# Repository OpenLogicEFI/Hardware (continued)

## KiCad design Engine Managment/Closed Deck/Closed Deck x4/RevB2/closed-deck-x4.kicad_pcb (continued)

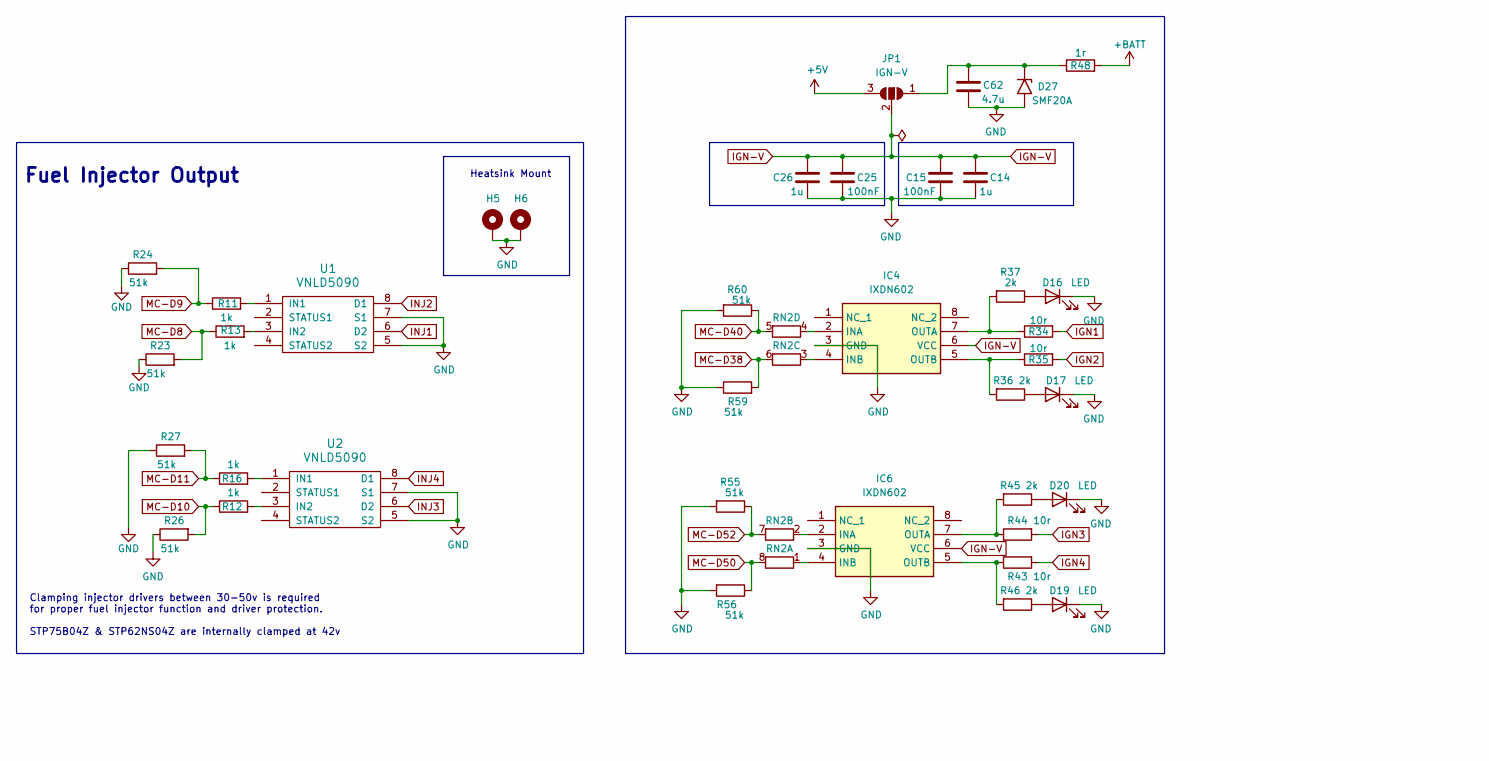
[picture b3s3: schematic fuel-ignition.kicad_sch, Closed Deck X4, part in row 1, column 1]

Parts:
C14, C26: 1u; C_0402_1005Metric; LCSC C52923
C15, C25: 100nF; C_0402_1005Metric; LCSC C307331
C62: 4.7u; C_1206_3216Metric; Manufacture Part Number 1206B475K500NT; LCSC C29823
D16, D17, D19, D20: LED; LED_0603_1608Metric; Manufacture Part Number KT-0603R; LCSC C2286
D27: SMF20A; D_SMF; LCSC C41411782
H5, H6: MountingHole_Pad; MountingHole_CD_Heatsink
IC4, IC6: IXDN602; SOIC-8_3.9x4.9mm_P1.27mm; Manufacture Part Number IXDN602; LCSC C431679
JP1: IGN-V; 1x03-Proto
R11, R12, R13, R16: 1k; R_0402_1005Metric; Manufacture Part Number 0402WGF1001TCE; LCSC C11702
R23, R24, R26, R27, R55, R56, R59, R60: 51k; R_0402_1005Metric; Manufacture Part Number 0402WGF5102TCE; LCSC C25794
R34, R35, R43, R44: 10r; R_0805_2012Metric; Manufacture Part Number 0805W8F100JT5E; LCSC C17415
R36, R37, R45, R46: 2k; R_0402_1005Metric; Manufacture Part Number 0402WGF2001TCE; LCSC C4109
R48: 1r; R_1206_3216Metric; Manufacture Part Number 1206W4F100KT5E; LCSC C17928
RN2: 1k; R_Array_Concave_4x0603; Manufacture Part Number 4D03WGJ0102T5E; LCSC C20197
U1, U2: VNLD5090; SO-8_3.9x4.9mm_P1.27mm_HandSoldering; LCSC C222209

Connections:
+5V: JP1.3 (B); also elsewhere on the board
+BATT: R48.2; also elsewhere on the board
GND: C14.2, C15.2, C25.2, C26.2, C62.2, D16.1 (K), D17.1 (K), D19.1 (K), D20.1 (K), D27.2 (A2), H5.1 (1_1), H6.1 (1_1), IC4.3 (GND), IC6.3 (GND), R23.1, R24.1, R26.1, R27.1, R55.2, R56.2, R59.1, R60.2, U1.5 (S2), U1.7 (S1), U2.5 (S2), U2.7 (S1); also elsewhere on the board
IGN1: R34.2; also elsewhere on the board
IGN2: R35.2; also elsewhere on the board
IGN3: R44.2; also elsewhere on the board
IGN4: R43.2; also elsewhere on the board
IGN-V: C14.1, C15.1, C25.1, C26.1, IC4.6 (VCC), IC6.6 (VCC), JP1.2 (C)
INJ1: U1.6 (D2); also elsewhere on the board
INJ2: U1.8 (D1); also elsewhere on the board
INJ3: U2.6 (D2); also elsewhere on the board
INJ4: U2.8 (D1); also elsewhere on the board
MC-D8: R13.1, R23.2; also elsewhere on the board
MC-D9: R11.1, R24.2; also elsewhere on the board
MC-D10: R12.1, R26.2; also elsewhere on the board
MC-D11: R16.1, R27.2; also elsewhere on the board
MC-D38: R59.2, RN2.6 (R3.2); also elsewhere on the board
MC-D40: R60.1, RN2.5 (R4.2); also elsewhere on the board
MC-D50: R56.1, RN2.8 (R1.2); also elsewhere on the board
MC-D52: R55.1, RN2.7 (R2.2); also elsewhere on the board
unnamed: D16.2 (A), R37.1
unnamed: D17.2 (A), R36.1
unnamed: D19.2 (A), R46.1
unnamed: D20.2 (A), R45.1
unnamed: C62.1, D27.1 (A1), JP1.1 (A), R48.1
unnamed: IC4.2 (INA), RN2.4 (R4.1)
unnamed: IC4.4 (INB), RN2.3 (R3.1)
unnamed: IC4.7 (OUTA), R34.1, R37.2
unnamed: IC4.5 (OUTB), R35.1, R36.2
unnamed: IC6.2 (INA), RN2.2 (R2.1)
unnamed: IC6.4 (INB), RN2.1 (R1.1)
unnamed: IC6.7 (OUTA), R44.1, R45.2
unnamed: IC6.5 (OUTB), R43.1, R46.2
unnamed: R11.2, U1.1 (IN1)
unnamed: R13.2, U1.3 (IN2)
unnamed: R16.2, U2.1 (IN1)
unnamed: R12.2, U2.3 (IN2)

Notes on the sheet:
Heatsink Mount
Clamping injector drivers between 30-50v is required for proper fuel injector function and driver protection. STP75B04Z & STP62NS04Z are internally clamped at 42v
Fuel Injector Output
Logic Level Ignition Output

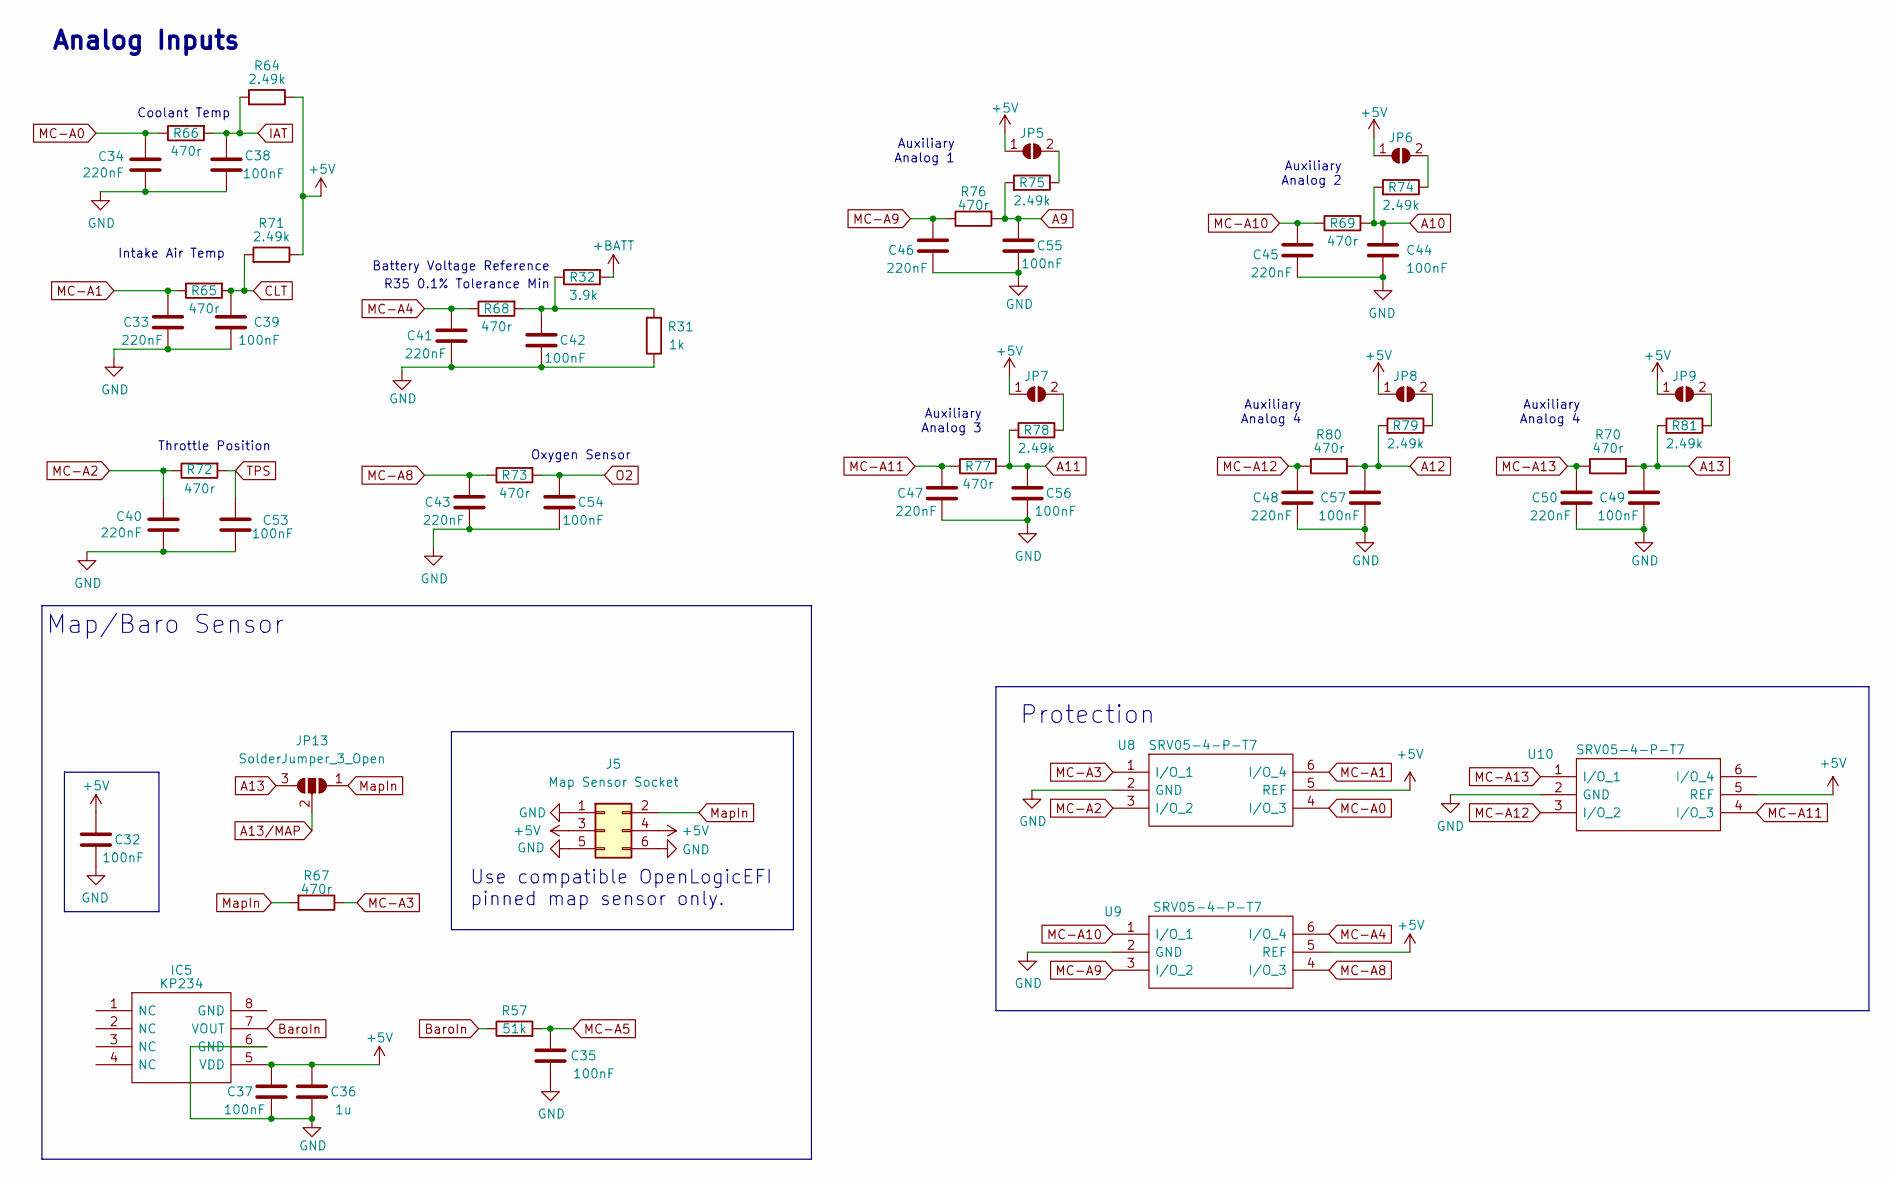
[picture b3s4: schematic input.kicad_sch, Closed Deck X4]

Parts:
C32, C37, C38, C39, C42, C44, C49, C53, C54, C55, C56, C57: 100nF; C_0402_1005Metric; LCSC C307331
C33, C34, C40, C41, C43, C45, C46, C47, C48, C50: 220nF; C_0402_1005Metric; LCSC C16772
C35: 100nF; C_0402_1005Metric; Manufacture Part Number CL05B104KB54PNC; LCSC C307331
C36: 1u; C_0402_1005Metric; LCSC C52923
IC5: KP234; KP234-Handsoldering; Manufacture Part Number KP234XTMA1
J5: Map Sensor Socket; PinSocket 2x03
JP5, JP6, JP7, JP8, JP9: SolderJumper_2_Open; SolderJumper-2_P1.3mm_Open_RoundedPad1.0x1.5mm
JP13: SolderJumper_3_Open; SolderJumper-3-OPEN
R31: 1k; R_0402_1005Metric; Manufacture Part Number 0402WGF1001TCE; LCSC C11702
R32: 3.9k; R_0603_1608Metric; Manufacture Part Number 0603WAF3901T5E; LCSC C23018
R57: 51k; R_0402_1005Metric; Manufacture Part Number 0402WGF5102TCE; LCSC C25794
R64, R71: 2.49k; R_Axial_DIN0207_L6.3mm_D2.5mm_P7.62mm_Horizontal
R65, R66, R67, R68, R69, R70, R72, R73, R76, R77, R80: 470r; R_0402_1005Metric; Manufacture Part Number 0402WGF4700TCE; LCSC C25117
R74, R75, R78, R79, R81: 2.49k; R_0402_1005Metric; Manufacture Part Number RC0402FR-072K49L; LCSC C145071
U8, U9, U10: SRV05-4-P-T7; SOT-23-6; LCSC C85364

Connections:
+5V: C32.2, C36.1, C37.1, IC5.5 (VDD), J5.3, J5.4, JP5.1 (A), JP6.1 (A), JP7.1 (A), JP8.1 (A), JP9.1 (A), R64.1, R71.1, U8.5 (REF), U9.5 (REF), U10.5 (REF); also elsewhere on the board
+BATT: R32.2; also elsewhere on the board
A9: C55.1, R75.2, R76.2; also elsewhere on the board
A10: C44.1, R69.2, R74.2; also elsewhere on the board
A11: C56.1, R77.2, R78.2; also elsewhere on the board
A12: C57.1, R79.2, R80.2; also elsewhere on the board
A13: C49.1, JP13.3 (B), R70.2, R81.2
A13/MAP: JP13.2 (C); also elsewhere on the board
BaroIn: IC5.7 (VOUT), R57.1
CLT: C39.1, R65.2, R71.2; also elsewhere on the board
GND: C32.1, C33.2, C34.2, C35.2, C36.2, C37.2, C38.2, C39.2, C40.2, C41.2, C42.2, C43.2, C44.2, C45.2, C46.2, C47.2, C48.2, C49.2, C50.2, C53.2, C54.2, C55.2, C56.2, C57.2, IC5.6 (GND), J5.1, J5.5, J5.6, R31.1, U8.2 (GND), U9.2 (GND), U10.2 (GND); also elsewhere on the board
IAT: C38.1, R64.2, R66.2; also elsewhere on the board
MC-A0: C34.1, R66.1, U8.4 (I/O_3); also elsewhere on the board
MC-A1: C33.1, R65.1, U8.6 (I/O_4); also elsewhere on the board
MC-A2: C40.1, R72.1, U8.3 (I/O_2); also elsewhere on the board
MC-A3: R67.1, U8.1 (I/O_1); also elsewhere on the board
MC-A4: C41.1, R68.1, U9.6 (I/O_4); also elsewhere on the board
MC-A5: C35.1, R57.2; also elsewhere on the board
MC-A8: C43.1, R73.1, U9.4 (I/O_3); also elsewhere on the board
MC-A9: C46.1, R76.1, U9.3 (I/O_2); also elsewhere on the board
MC-A10: C45.1, R69.1, U9.1 (I/O_1); also elsewhere on the board
MC-A11: C47.1, R77.1, U10.4 (I/O_3); also elsewhere on the board
MC-A12: C48.1, R80.1, U10.3 (I/O_2); also elsewhere on the board
MC-A13: C50.1, R70.1, U10.1 (I/O_1); also elsewhere on the board
MapIn: J5.2, JP13.1 (A), R67.2
unnamed: C42.1, R31.2, R32.1, R68.2
unnamed: JP5.2 (B), R75.1
unnamed: JP6.2 (B), R74.1
unnamed: JP7.2 (B), R78.1
unnamed: JP8.2 (B), R79.1
unnamed: JP9.2 (B), R81.1
O2: C54.1, R73.2; also elsewhere on the board
TPS: C53.1, R72.2; also elsewhere on the board

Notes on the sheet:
Analog Inputs
Throttle Position
Auxiliary Analog 2
Auxiliary Analog 4
Auxiliary Analog 1
R35 0.1% Tolerance Min
Oxygen Sensor
Map/Baro Sensor
Use compatible OpenLogicEFI pinned map sensor only.
Coolant Temp
Intake Air Temp
Battery Voltage Reference
Protection
Auxiliary Analog 3

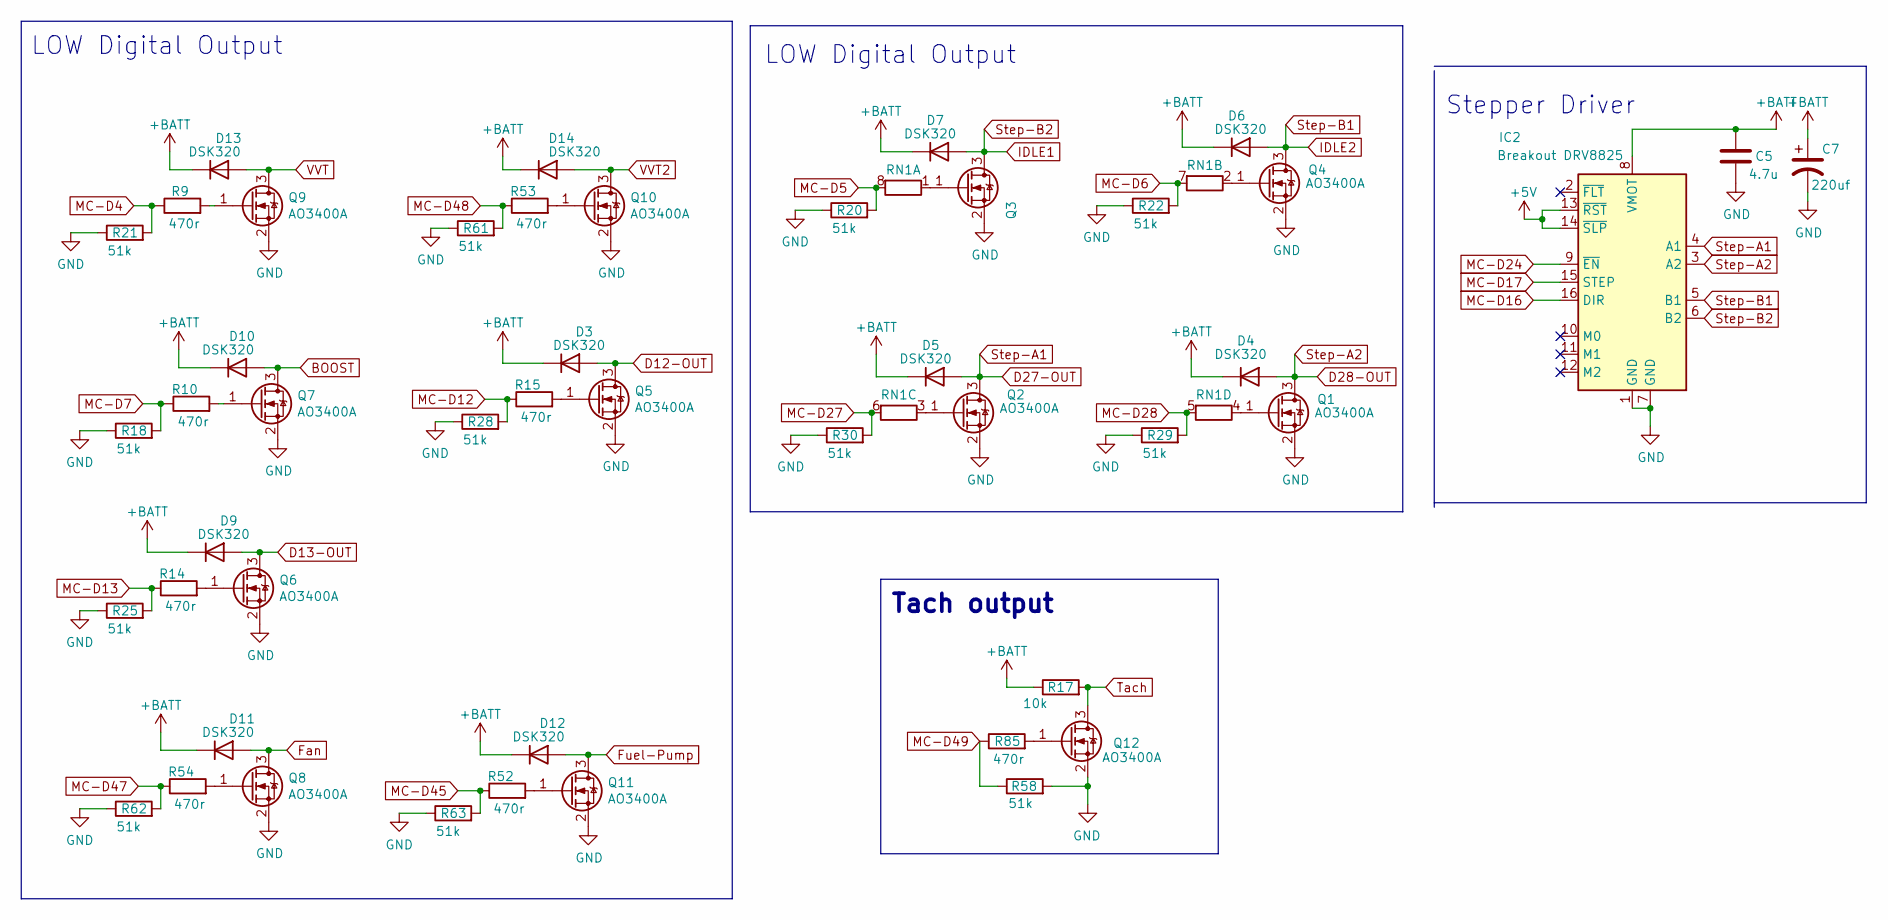
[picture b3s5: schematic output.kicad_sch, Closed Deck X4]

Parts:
C5: 4.7u; C_1206_3216Metric; Manufacture Part Number 1206B475K500NT; LCSC C29823
C7: 220uf; CP_Radial_D6.3mm_P2.50mm
D3, D4, D5, D6, D7, D9, D10, D11, D12, D13, D14: DSK320; D_SOD-123F; JLC C2128
IC2: Breakout DRV8825; DVR8825-Labeled-Front
Q1, Q2, Q3, Q4, Q5, Q6, Q12: AO3400A; SOT-23; Manufacture Part Number AO3400A; LCSC C20917
Q7, Q8, Q9, Q10, Q11: AO3400A; SOT-23; Manufacture Part Number AO3400A; JLC C20917
R9, R10, R14, R15, R52, R53, R54, R85: 470r; R_0402_1005Metric; Manufacture Part Number 0402WGF4700TCE; LCSC C25117
R17: 10k; R_0402_1005Metric; Manufacture Part Number 0402WGF1002TCE; LCSC C25744
R18, R20, R21, R22, R25, R28, R29, R30, R58, R61, R62, R63: 51k; R_0402_1005Metric; Manufacture Part Number 0402WGF5102TCE; LCSC C25794
RN1: 1k; R_Array_Concave_4x0603; Manufacture Part Number 4D03WGJ0102T5E; LCSC C20197

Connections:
+5V: IC2.13 (~RST), IC2.14 (~SLP); also elsewhere on the board
+BATT: C5.1, C7.1, D3.1 (K), D4.1 (K), D5.1 (K), D6.1 (K), D7.1 (K), D9.1 (K), D10.1 (K), D11.1 (K), D12.1 (K), D13.1 (K), D14.1 (K), IC2.8 (VMOT), R17.1; also elsewhere on the board
BOOST: D10.2 (A), Q7.3 (D); also elsewhere on the board
D12-OUT: D3.2 (A), Q5.3 (D); also elsewhere on the board
D13-OUT: D9.2 (A), Q6.3 (D); also elsewhere on the board
D27-OUT: D5.2 (A), IC2.4 (A1), Q2.3 (D); also elsewhere on the board
D28-OUT: D4.2 (A), IC2.3 (A2), Q1.3 (D); also elsewhere on the board
Fan: D11.2 (A), Q8.3 (D); also elsewhere on the board
Fuel-Pump: D12.2 (A), Q11.3 (D); also elsewhere on the board
GND: C5.2, C7.2, IC2.1 (GND), IC2.7 (GND), Q1.2 (S), Q2.2 (S), Q3.2 (S), Q4.2 (S), Q5.2 (S), Q6.2 (S), Q7.2 (S), Q8.2 (S), Q9.2 (S), Q10.2 (S), Q11.2 (S), Q12.2 (S), R18.1, R20.1, R21.1, R22.1, R25.1, R28.1, R29.1, R30.1, R58.2, R61.1, R62.1, R63.1; also elsewhere on the board
IDLE1: D7.2 (A), IC2.6 (B2), Q3.3 (D); also elsewhere on the board
IDLE2: D6.2 (A), IC2.5 (B1), Q4.3 (D); also elsewhere on the board
MC-D4: R9.1, R21.2; also elsewhere on the board
MC-D5: R20.2, RN1.8 (R1.2); also elsewhere on the board
MC-D6: R22.2, RN1.7 (R2.2); also elsewhere on the board
MC-D7: R10.1, R18.2; also elsewhere on the board
MC-D12: R15.1, R28.2; also elsewhere on the board
MC-D13: R14.1, R25.2; also elsewhere on the board
MC-D16: IC2.16 (DIR); also elsewhere on the board
MC-D17: IC2.15 (STEP); also elsewhere on the board
MC-D24: IC2.9 (~EN); also elsewhere on the board
MC-D27: R30.2, RN1.6 (R3.2); also elsewhere on the board
MC-D28: R29.2, RN1.5 (R4.2); also elsewhere on the board
MC-D45: R52.1, R63.2; also elsewhere on the board
MC-D47: R54.1, R62.2; also elsewhere on the board
MC-D48: R53.1, R61.2; also elsewhere on the board
MC-D49: R58.1, R85.1; also elsewhere on the board
unnamed: Q1.1 (G), RN1.4 (R4.1)
unnamed: Q2.1 (G), RN1.3 (R3.1)
unnamed: Q3.1 (G), RN1.1 (R1.1)
unnamed: Q4.1 (G), RN1.2 (R2.1)
unnamed: Q5.1 (G), R15.2
unnamed: Q6.1 (G), R14.2
unnamed: Q7.1 (G), R10.2
unnamed: Q8.1 (G), R54.2
unnamed: Q9.1 (G), R9.2
unnamed: Q10.1 (G), R53.2
unnamed: Q11.1 (G), R52.2
unnamed: Q12.1 (G), R85.2
Tach: Q12.3 (D), R17.2; also elsewhere on the board
VVT: D13.2 (A), Q9.3 (D); also elsewhere on the board
VVT2: D14.2 (A), Q10.3 (D); also elsewhere on the board

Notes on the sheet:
Tach output
LOW Digital Output
Stepper Driver

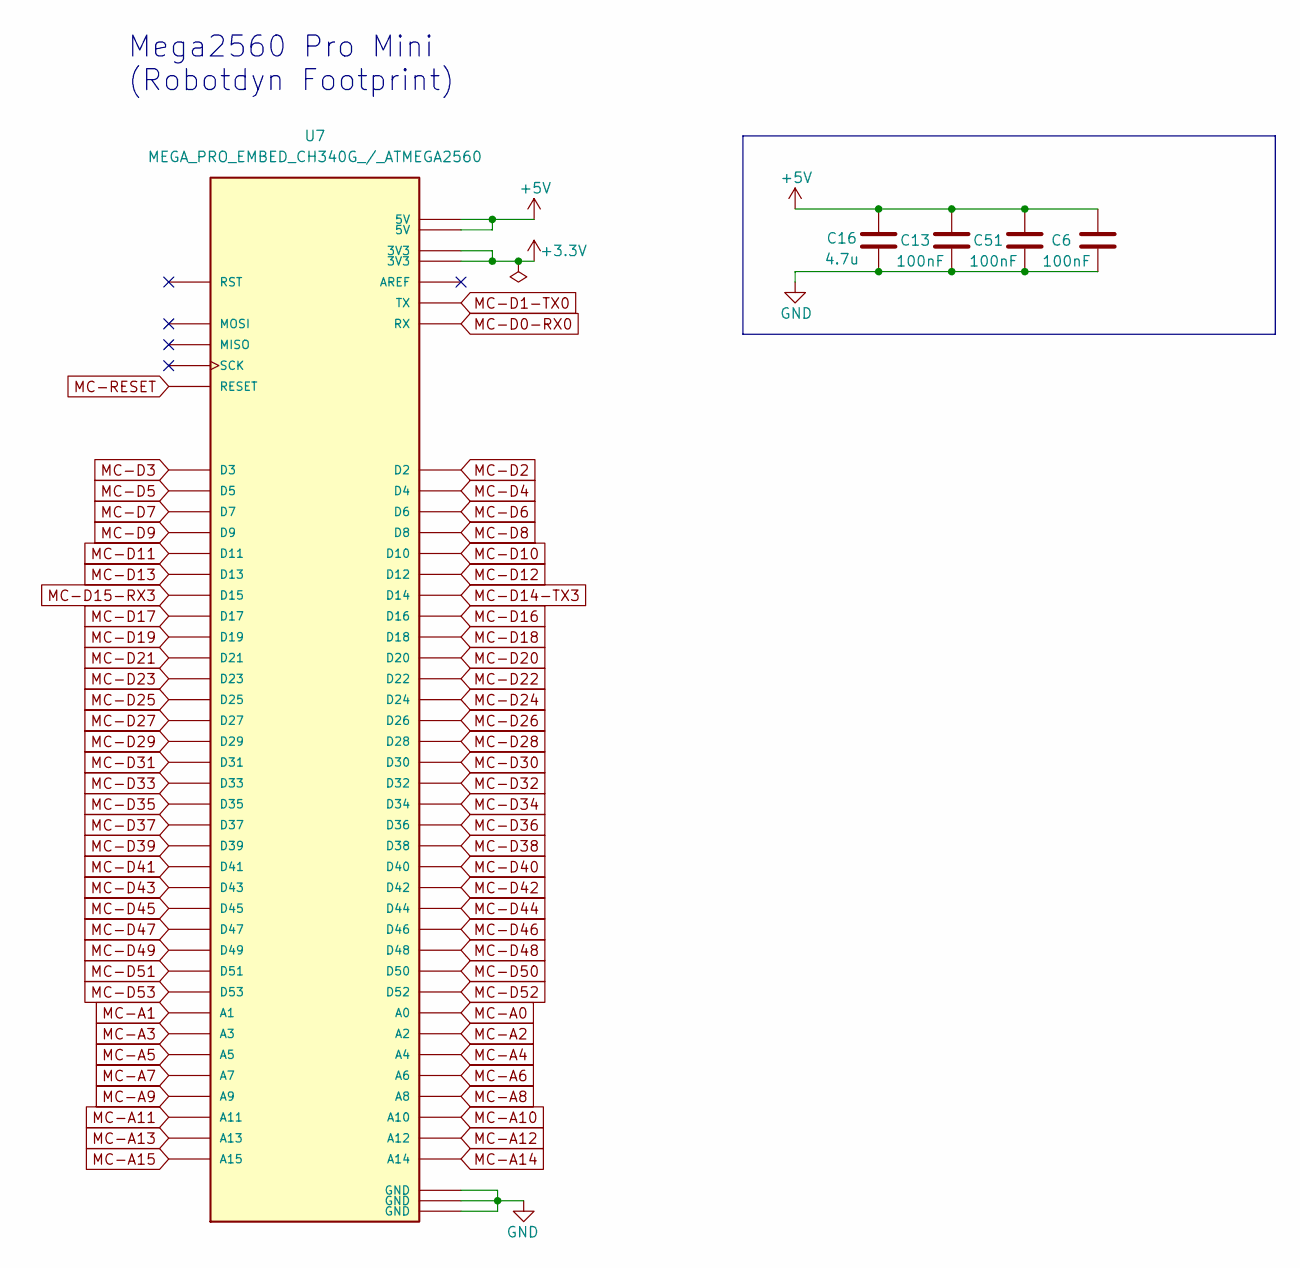
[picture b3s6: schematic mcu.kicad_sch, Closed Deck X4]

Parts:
C6, C13, C51: 100nF; C_0402_1005Metric; LCSC C307331
C16: 4.7u; C_1206_3216Metric; Manufacture Part Number 1206B475K500NT; LCSC C29823
U7: MEGA_PRO_EMBED_CH340G_/_ATMEGA2560; Arduino_Mega_Mini_2560_SmallCrtYd_NoVin

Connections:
+3.3V: U7.3V3_1 (3V3), U7.3V3_2 (3V3)
+5V: C6.2, C13.2, C16.1, C51.2, U7.5V_1 (5V), U7.5V_2 (5V), U7.5V_3 (5V); also elsewhere on the board
GND: C6.1, C13.1, C16.2, C51.1, U7.GND_1 (GND), U7.GND_2 (GND), U7.GND_3 (GND); also elsewhere on the board
MC-A0: U7.A0; also elsewhere on the board
MC-A1: U7.A1; also elsewhere on the board
MC-A2: U7.A2; also elsewhere on the board
MC-A3: U7.A3; also elsewhere on the board
MC-A4: U7.A4; also elsewhere on the board
MC-A5: U7.A5; also elsewhere on the board
MC-A6: U7.A6
MC-A7: U7.A7
MC-A8: U7.A8; also elsewhere on the board
MC-A9: U7.A9; also elsewhere on the board
MC-A10: U7.A10; also elsewhere on the board
MC-A11: U7.A11; also elsewhere on the board
MC-A12: U7.A12; also elsewhere on the board
MC-A13: U7.A13; also elsewhere on the board
MC-A14: U7.A14
MC-A15: U7.A15
MC-D0-RX0: U7.RX; also elsewhere on the board
MC-D1-TX0: U7.TX; also elsewhere on the board
MC-D2: U7.D2; also elsewhere on the board
MC-D3: U7.D3; also elsewhere on the board
MC-D4: U7.D4; also elsewhere on the board
MC-D5: U7.D5; also elsewhere on the board
MC-D6: U7.D6; also elsewhere on the board
MC-D7: U7.D7; also elsewhere on the board
MC-D8: U7.D8; also elsewhere on the board
MC-D9: U7.D9; also elsewhere on the board
MC-D10: U7.D10; also elsewhere on the board
MC-D11: U7.D11; also elsewhere on the board
MC-D12: U7.D12; also elsewhere on the board
MC-D13: U7.D13; also elsewhere on the board
MC-D14-TX3: U7.D14; also elsewhere on the board
MC-D15-RX3: U7.D15; also elsewhere on the board
MC-D16: U7.D16; also elsewhere on the board
MC-D17: U7.D17; also elsewhere on the board
MC-D18: U7.D18; also elsewhere on the board
MC-D19: U7.D19; also elsewhere on the board
MC-D20: U7.D20; also elsewhere on the board
MC-D21: U7.D21; also elsewhere on the board
MC-D22: U7.D22; also elsewhere on the board
MC-D23: U7.D23; also elsewhere on the board
MC-D24: U7.D24; also elsewhere on the board
MC-D25: U7.D25
MC-D26: U7.D26
MC-D27: U7.D27; also elsewhere on the board
MC-D28: U7.D28; also elsewhere on the board
MC-D29: U7.D29
MC-D30: U7.D30
MC-D31: U7.D31
MC-D32: U7.D32
MC-D33: U7.D33
MC-D34: U7.D34
MC-D35: U7.D35
MC-D36: U7.D36
MC-D37: U7.D37
MC-D38: U7.D38; also elsewhere on the board
MC-D39: U7.D39
MC-D40: U7.D40; also elsewhere on the board
MC-D41: U7.D41
MC-D42: U7.D42
MC-D43: U7.D43
MC-D44: U7.D44
MC-D45: U7.D45; also elsewhere on the board
MC-D46: U7.D46
MC-D47: U7.D47; also elsewhere on the board
MC-D48: U7.D48; also elsewhere on the board
MC-D49: U7.D49; also elsewhere on the board
MC-D50: U7.D50; also elsewhere on the board
MC-D51: U7.D51; also elsewhere on the board
MC-D52: U7.D52; also elsewhere on the board
MC-D53: U7.D53
MC-RESET: U7.RESET; also elsewhere on the board

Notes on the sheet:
Mega2560 Pro Mini (Robotdyn Footprint)

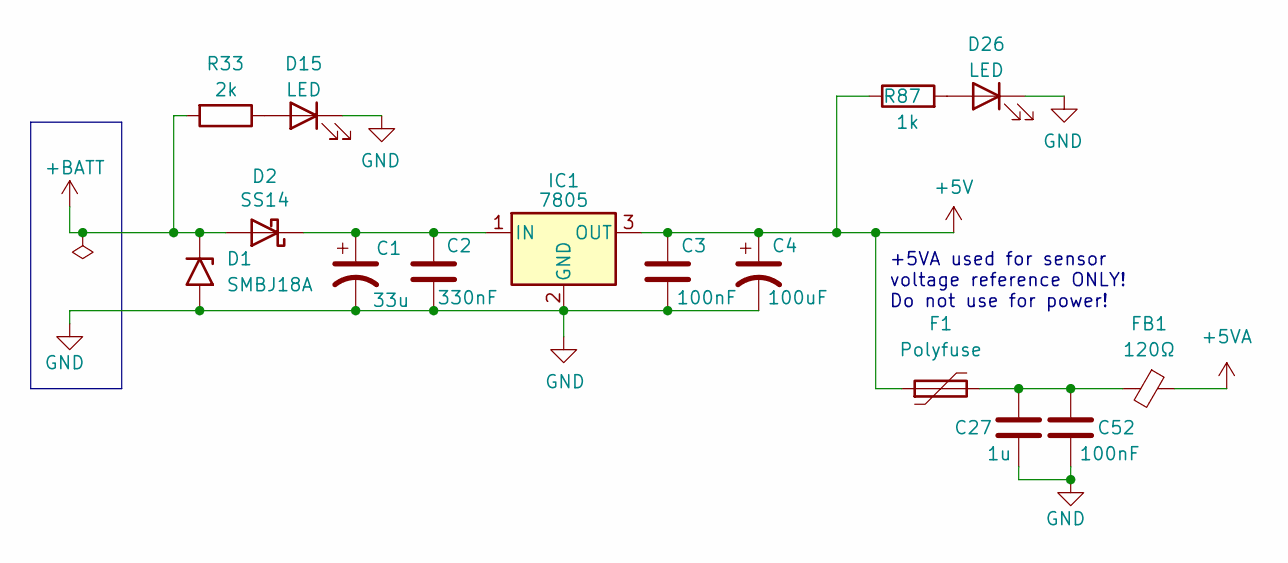
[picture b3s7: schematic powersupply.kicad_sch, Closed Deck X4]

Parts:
C1: 33u; CP_EIA-6032-28_Kemet-C; Manufacture Part Number TAJC106K035RNJ; LCSC C7211
C2: 330nF; C_0805_2012Metric; Manufacture Part Number 0805B334K500NT; LCSC C1740
C3: 100nF; C_0805_2012Metric; Manufacture Part Number CC0805KRX7R9BB104; LCSC C49678
C4: 100uF; CP_EIA-3528-15_AVX-H; Manufacture Part Number TAJB107K006RNJ; LCSC C16133
C27: 1u; C_0402_1005Metric; LCSC C52923
C52: 100nF; C_0402_1005Metric; LCSC C307331
D1: SMBJ18A; D_SMB; LCSC C19077573
D2: SS14; D_SMA; Manufacture Part Number SS14; LCSC C2480
D15, D26: LED; LED_0603_1608Metric; Manufacture Part Number KT-0603R; LCSC C2286
F1: Polyfuse; Fuse_1206_3216Metric; LCSC C976305
FB1: 120Ω; C_0603_1608Metric; Manufacture Part Number BLM18PG121SN1D; LCSC C14709
IC1: 7805; TO-263-2; Manufacture Part Number L78M05ABDT-TR; LCSC C86206
R33: 2k; R_0402_1005Metric; Manufacture Part Number 0402WGF2001TCE; LCSC C4109
R87: 1k; R_0402_1005Metric; Manufacture Part Number 0402WGF1001TCE; LCSC C11702

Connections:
+5V: C3.1, C4.1, F1.1, IC1.3 (OUT), R87.1; also elsewhere on the board
+5VA: FB1.1; also elsewhere on the board
+BATT: D1.1 (A1), D2.2 (A), R33.2; also elsewhere on the board
GND: C1.2, C2.2, C3.2, C4.2, C27.2, C52.2, D1.2 (A2), D15.1 (K), D26.1 (K), IC1.2 (GND); also elsewhere on the board
unnamed: C27.1, C52.1, F1.2, FB1.2
unnamed: C1.1, C2.1, D2.1 (K), IC1.1 (IN)
unnamed: D15.2 (A), R33.1
unnamed: D26.2 (A), R87.2

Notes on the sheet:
+5VA used for sensor voltage reference ONLY! Do not use for power!

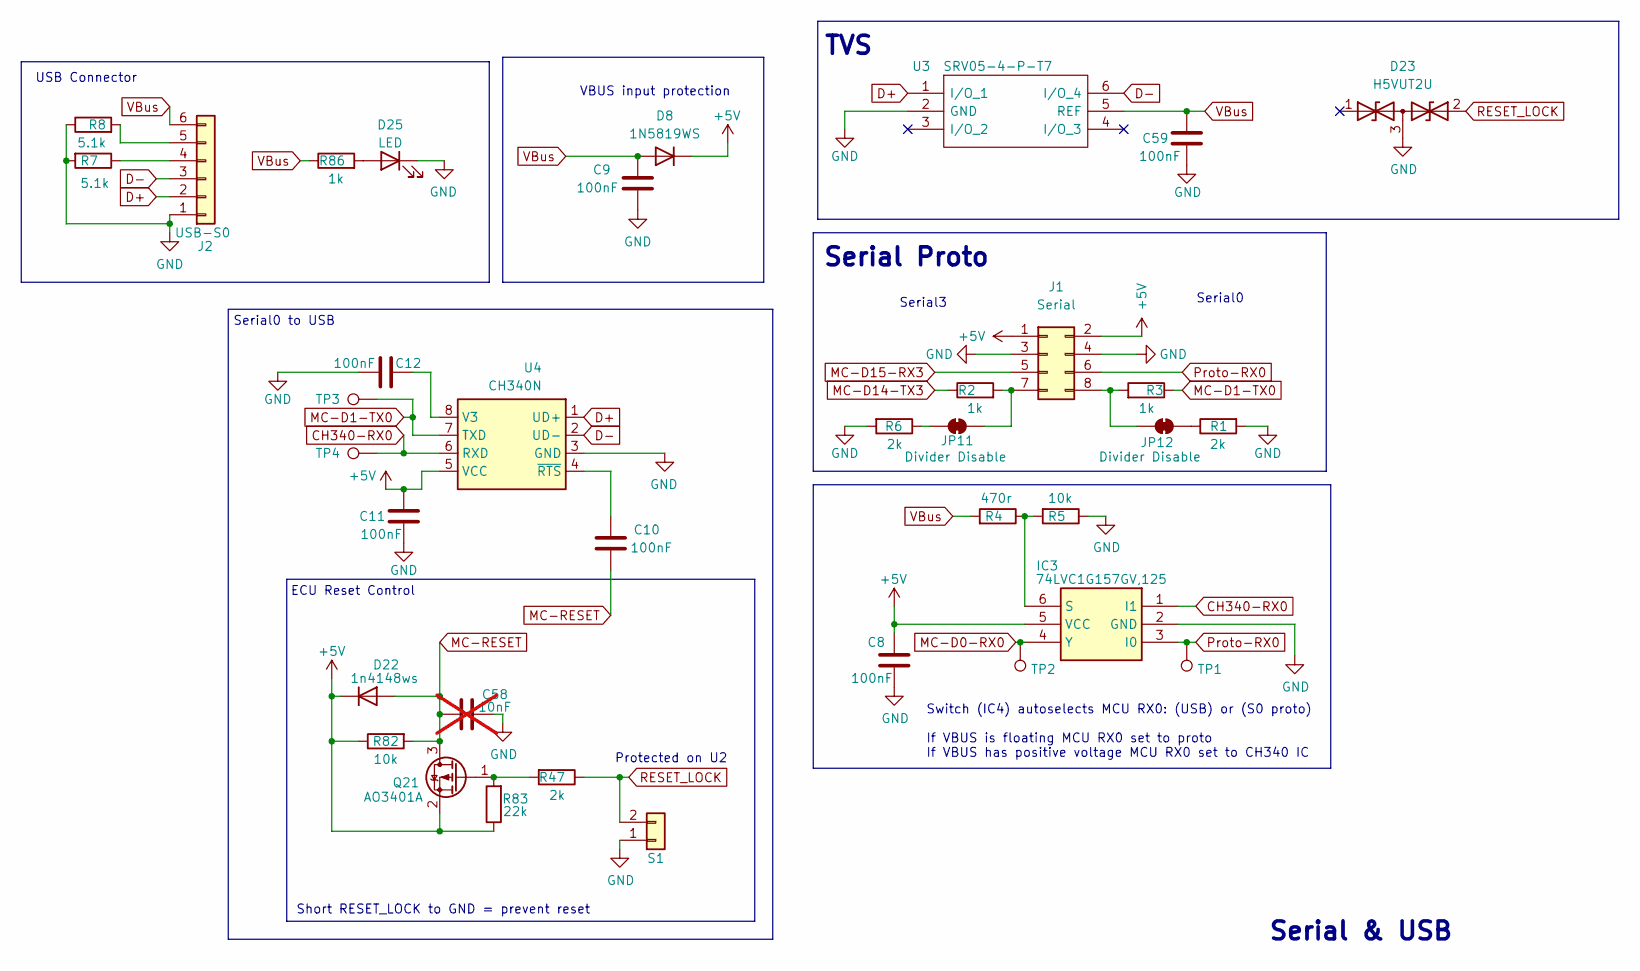
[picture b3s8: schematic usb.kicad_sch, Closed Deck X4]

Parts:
C8, C9, C10, C11, C12, C59: 100nF; C_0402_1005Metric; LCSC C307331
C58: 10nF; C_0402_1005Metric; Manufacture Part Number CL05B103KB5NNNC; LCSC C15195; not fitted
D8: 1N5819WS; D_SOD-323; Manufacture Part Number 1N5819WS; LCSC C191023
D22: 1n4148ws; D_SOD-323; LCSC C2128
D23: H5VUT2U; SOT-23; LCSC C20615824
D25: LED; LED_0603_1608Metric; Manufacture Part Number KT-0603R; LCSC C2286
IC3: 74LVC1G157GV,125; TSOT-23-6; Manufacture Part Number 74LVC1G157GW,125; LCSC C53114339
J1: Serial; 2x04-2.54mm-Serial-withSilk
J2: USB-S0; JST_PH_B6B-PH-K_1x06_P2.00mm_Vertical
JP11, JP12: Divider Disable; SolderJumper-2_P1.3mm_Bridged_RoundedPad1.0x1.5mm
Q21: AO3401A; SOT-23; Manufacture Part Number AO3401A; LCSC C15127
R1, R6, R47: 2k; R_0402_1005Metric; Manufacture Part Number 0402WGF2001TCE; LCSC C4109
R2, R3, R86: 1k; R_0402_1005Metric; Manufacture Part Number 0402WGF1001TCE; LCSC C11702
R4: 470r; R_0402_1005Metric; Manufacture Part Number 0402WGF4700TCE; LCSC C25117
R5, R82: 10k; R_0402_1005Metric; Manufacture Part Number 0402WGF1002TCE; LCSC C25744
R7, R8: 5.1k; R_0402_1005Metric; Manufacture Part Number 0402WGF5101TCE; LCSC C25905
R83: 22k; R_0402_1005Metric; LCSC C25768
S1: Reset Control; PinHeader_1x02_P2.54mm_Vertical
TP1, TP2, TP3, TP4: TestPoint; TestPoint_THT_D0.6mm_Drill0.3mm
U3: SRV05-4-P-T7; SOT-23-6; LCSC C85364
U4: CH340N; SOIC-8_3.9x4.9mm_P1.27mm; LCSC C2977777

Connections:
+5V: C8.2, C11.1, D8.1 (K), D22.1 (K), IC3.5 (VCC), J1.1, J1.2, Q21.2 (S), R82.1, R83.1, U4.5 (VCC); also elsewhere on the board
CH340-RX0: IC3.1 (I1), TP4.1 (1_1), U4.6 (RXD)
D+: J2.2, U3.1 (I/O_1), U4.1 (UD+)
D-: J2.3, U3.6 (I/O_4), U4.2 (UD-)
GND: C8.1, C9.2, C11.2, C12.2, C58.1, C59.1, D23.3 (common), D25.1 (K), IC3.2 (GND), J1.3, J1.4, J2.1, R1.2, R5.1, R6.2, R7.2, R8.1, S1.1, U3.2 (GND), U4.3 (GND); also elsewhere on the board
MC-D0-RX0: IC3.4 (Y), TP2.1 (1_1); also elsewhere on the board
MC-D1-TX0: R3.1, TP3.1 (1_1), U4.7 (TXD); also elsewhere on the board
MC-D14-TX3: R2.1; also elsewhere on the board
MC-D15-RX3: J1.5; also elsewhere on the board
MC-RESET: C10.2, C58.2, D22.2 (A), Q21.3 (D), R82.2; also elsewhere on the board
unnamed: D25.2 (A), R86.2
unnamed: IC3.6 (S), R4.1, R5.2
unnamed: J1.7, JP11.2 (B), R2.2
unnamed: J1.8, JP12.1 (A), R3.2
unnamed: J2.4, R7.1
unnamed: J2.5, R8.2
unnamed: JP11.1 (A), R6.1
unnamed: JP12.2 (B), R1.1
unnamed: Q21.1 (G), R47.2, R83.2
unnamed: C12.1, U4.8 (V3)
unnamed: C10.1, U4.4 (~RTS)
Proto-RX0: IC3.3 (I0), J1.6, TP1.1 (1_1)
RESET_LOCK: D23.2 (A2), R47.1, S1.2
VBus: C9.1, C59.2, D8.2 (A), J2.6, R4.2, R86.1, U3.5 (REF)

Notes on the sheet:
Serial0
TVS
VBUS input protection
Switch (IC4) autoselects MCU RX0: (USB) or (S0 proto) If VBUS is floating MCU RX0 set to proto If VBUS has positive voltage MCU RX0 set to CH340 IC
Protected on U2
Serial & USB
ECU Reset Control
Short RESET_LOCK to GND = prevent reset
Serial3
Serial0 to USB
USB Connector
Serial Proto

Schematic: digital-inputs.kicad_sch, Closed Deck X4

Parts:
C17, C19, C28, C29: 100nF; C_0402_1005Metric; LCSC C307331
C18: 220nF; C_0402_1005Metric; LCSC C16772
C20, C21, C22, C23, C24, C30: 10nF; C_0402_1005Metric; Manufacture Part Number CL05B103KB5NNNC; LCSC C15195
D18: BZT52C6V2S; D_SOD-323; LCSC C19077442
D21, D24: H5VUT2U; SOT-23; LCSC C20615824
J3: VR Conditioner; Socket_VRConditioner_Corrected
J4: Input Jumper; PinHeader2x03_Jumper
JP2, JP3, JP4, JP10: FET Bypass; SolderJumper-2_P1.3mm_Open_RoundedPad1.0x1.5mm
Q13, Q14, Q15, Q16, Q17, Q18, Q19, Q20: 2N7002K; SOT-23; Manufacture Part Number 2N7002K; LCSC C22379475
R19: 2.2k; R_0402_1005Metric; Manufacture Part Number 0402WGF2201TCE; LCSC C25879
R38, R39, R40, R41, R42, R49, R50, R51: 1k; R_0402_1005Metric; Manufacture Part Number 0402WGF1001TCE; LCSC C11702
R84: 470r; R_0402_1005Metric; Manufacture Part Number 0402WGF4700TCE; LCSC C25117
U11: SRV05-4-P-T7; SOT-23-6; LCSC C85364

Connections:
+5V: C28.2, C29.2, J3.5, Q13.1 (G), Q14.1 (G), Q15.1 (G), Q16.1 (G), Q17.1 (G), Q18.1 (G), Q19.1 (G), Q20.1 (G), R19.1, R38.1, R39.1, R40.1, R41.1, R42.1, R49.1, R50.1, R51.1, U11.5 (REF); also elsewhere on the board
Cam2: JP2.1 (A), Q13.3 (D); also elsewhere on the board
Cam-Direct: J4.b3, JP3.1 (A), Q18.3 (D)
Cam-In: J4.b2; also elsewhere on the board
Clutch: Q20.3 (D); also elsewhere on the board
Crank-Direct: J4.a3, JP4.1 (A), Q19.3 (D)
Crank-In: J4.a2; also elsewhere on the board
D21-IN: Q15.3 (D); also elsewhere on the board
D22-IN: Q17.3 (D); also elsewhere on the board
D23-IN: Q16.3 (D); also elsewhere on the board
Flex: C18.1, D18.1 (A1), D24.2 (A2), R19.2, R84.1; also elsewhere on the board
GND: C17.1, C18.2, C19.1, C20.2, C21.1, C22.2, C23.2, C24.2, C28.1, C29.1, C30.2, D18.2 (A2), D21.3 (common), D24.3 (common), J3.6, U11.2 (GND); also elsewhere on the board
MC-D2: R84.2; also elsewhere on the board
MC-D3: C17.2, D24.1 (A1), JP2.2 (B), Q13.2 (S), R38.2; also elsewhere on the board
MC-D18: C19.2, D21.1 (A1), J3.7, JP3.2 (B), Q18.2 (S), R49.2; also elsewhere on the board
MC-D19: C21.2, D21.2 (A2), J3.8, JP4.2 (B), Q19.2 (S), R50.2; also elsewhere on the board
MC-D20: C20.1, JP10.2 (B), Q14.2 (S), R39.2, U11.6 (I/O_4); also elsewhere on the board
MC-D21: C22.1, Q15.2 (S), R40.2, U11.4 (I/O_3); also elsewhere on the board
MC-D22: C23.1, Q17.2 (S), R41.2, U11.1 (I/O_1); also elsewhere on the board
MC-D23: C24.1, Q16.2 (S), R42.2, U11.3 (I/O_2); also elsewhere on the board
MC-D51: C30.1, Q20.2 (S), R51.2; also elsewhere on the board
VR1+: J3.2, J4.a1
VR1-: J3.1; also elsewhere on the board
VR2+: J3.3, J4.b1
VR2-: J3.4; also elsewhere on the board
VSS-IN: JP10.1 (A), Q14.3 (D); also elsewhere on the board

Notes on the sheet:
Vehicle Speed Sensor Input
JP May Be required with VR Conditioner
Protection
Cam
Speeduino Compatible VR Mount
Clutch Switch (GND Switched)
Ethanol Sensor
Usage Jumper
Crank
Crank/Cam Sensor Input
Cam2
Digital Inputs
